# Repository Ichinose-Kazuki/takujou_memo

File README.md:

# takujou_memo

* サーバ側処理：server フォントのパスを変更しないとWindowsで使えないので注意してください
* ESP32側コード最終版：tcp_and_spiffs_and_eink

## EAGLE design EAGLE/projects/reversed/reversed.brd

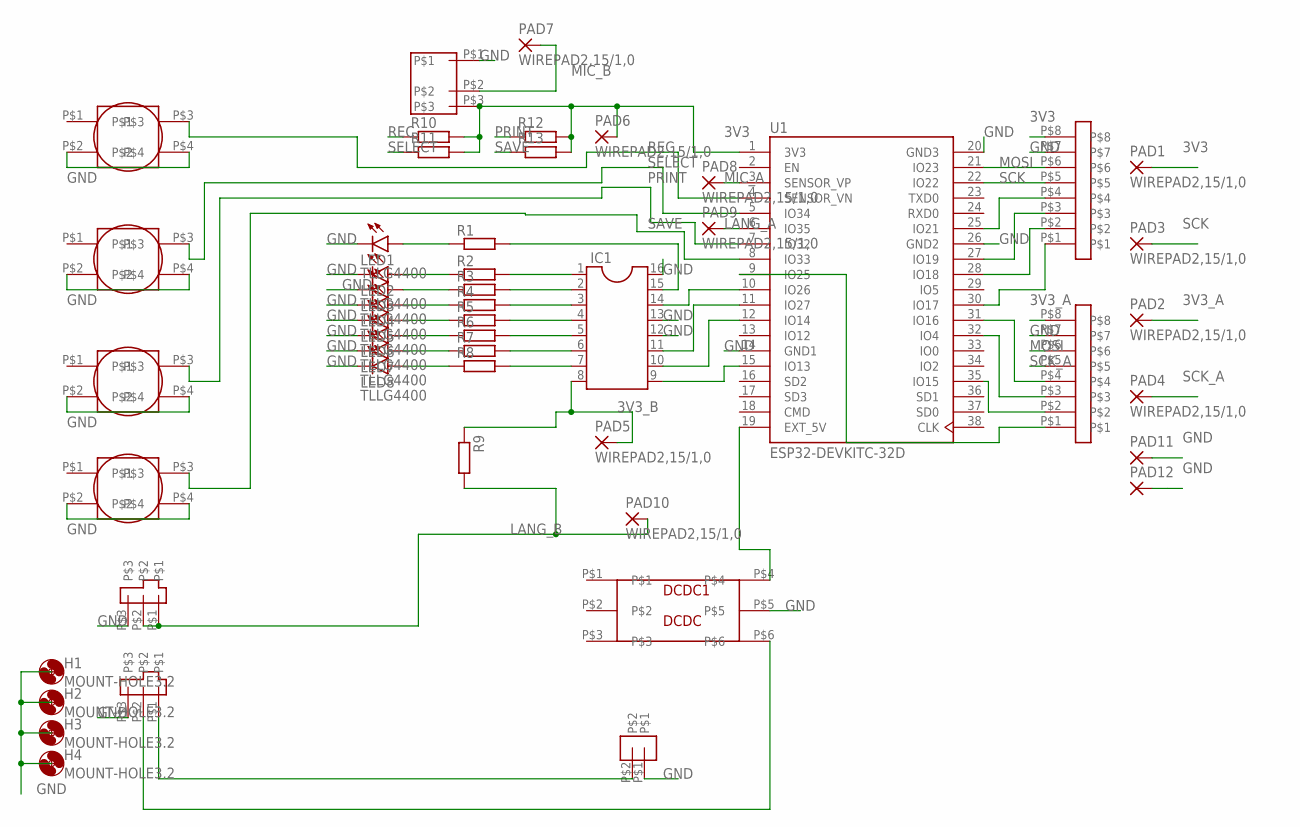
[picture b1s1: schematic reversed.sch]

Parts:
BATTERY1: BATTERY
DCDC1: DCDC
DISPLAY1, DISPLAY2: DISPLAY
H1, H2, H3, H4: MOUNT-HOLE3.2; 3,2
IC1: DIL16S; SOCKET-16
LED1, LED2, LED3, LED4, LED5, LED6, LED7, LED8: TLLG4400; LED3MM
MIC1: MIC
PAD1, PAD2, PAD3, PAD4, PAD5, PAD6, PAD7, PAD8, PAD9, PAD10: WIREPAD2,15/1,0; 2,15/1,0
PAD11, PAD12: 2,15/1,0
R1, R2, R3, R4, R5, R6, R7, R8: SMK
R9, R10, R11, R12, R13: R-EU_0207/10; 0207/10
SWITCH1, SWITCH2, SWITCH3, SWITCH4: SWITCH
TOGGLE1, TOGGLE2: TOGGLE
U1: ESP32-DEVKITC-32D; MODULE_ESP32-DEVKITC-32D

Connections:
3V3: DISPLAY1.P$8, MIC1.P$3, PAD1.1, PAD6.1, R10.2, R11.2, R12.2, R13.2, U1.1 (3V3)
3V3_A: DISPLAY2.P$8, PAD2.1
3V3_B: IC1.8, PAD5.1, R9.1
GND: BATTERY1.P$1, DCDC1.P$5, DISPLAY1.P$7, DISPLAY2.P$7, IC1.12, IC1.13, IC1.16, LED1.K (C), LED2.K (C), LED3.K (C), LED4.K (C), LED5.K (C), LED6.K (C), LED7.K (C), LED8.K (C), MIC1.P$1, PAD11.1, PAD12.1, SWITCH1.P$2, SWITCH1.P$4, SWITCH2.P$2, SWITCH2.P$4, SWITCH3.P$2, SWITCH3.P$4, SWITCH4.P$2, SWITCH4.P$4, TOGGLE1.P$3, TOGGLE2.P$3, U1.14 (GND1), U1.20 (GND3), U1.26 (GND2)
LANG_A: PAD9.1, U1.6 (IO35)
LANG_B: PAD10.1, R9.2, TOGGLE1.P$1, TOGGLE1.P$2
MIC_A: PAD8.1, U1.3 (SENSOR_VP)
MIC_B: MIC1.P$2, PAD7.1
MOSI: DISPLAY1.P$6, DISPLAY2.P$6, U1.21 (IO23)
unnamed: DISPLAY1.P$4, U1.25 (IO21)
unnamed: DISPLAY1.P$3, U1.27 (IO19)
unnamed: DISPLAY1.P$2, U1.28 (IO18)
unnamed: DISPLAY1.P$1, U1.30 (IO17)
unnamed: DISPLAY2.P$4, U1.31 (IO16)
unnamed: DISPLAY2.P$3, U1.32 (IO4)
unnamed: DISPLAY2.P$2, U1.35 (IO15)
unnamed: DISPLAY2.P$1, U1.9 (IO25)
unnamed: IC1.9, U1.15 (IO13)
unnamed: IC1.10, U1.12 (IO14)
unnamed: IC1.11, U1.11 (IO27)
unnamed: IC1.14, U1.10 (IO26)
unnamed: IC1.15, R1.1
unnamed: IC1.1, R2.1
unnamed: IC1.2, R3.1
unnamed: IC1.3, R4.1
unnamed: IC1.4, R5.1
unnamed: IC1.5, R6.1
unnamed: IC1.6, R7.1
unnamed: IC1.7, R8.1
unnamed: DCDC1.P$4, U1.19 (EXT_5V)
unnamed: LED1.A, R1.2
unnamed: LED2.A, R2.2
unnamed: LED3.A, R3.2
unnamed: LED4.A, R4.2
unnamed: LED5.A, R5.2
unnamed: LED6.A, R6.2
unnamed: LED7.A, R7.2
unnamed: LED8.A, R8.2
unnamed: DCDC1.P$6, TOGGLE2.P$2
unnamed: BATTERY1.P$2, TOGGLE2.P$1
PRINT: R12.1, SWITCH3.P$3, U1.7 (IO32)
REC: R10.1, SWITCH1.P$3, U1.4 (SENSOR_VN)
SAVE: R13.1, SWITCH4.P$3, U1.8 (IO33)
SCK: DISPLAY1.P$5, PAD3.1, U1.22 (IO22)
SCK_A: DISPLAY2.P$5, PAD4.1
SELECT: R11.1, SWITCH2.P$3, U1.5 (IO34)

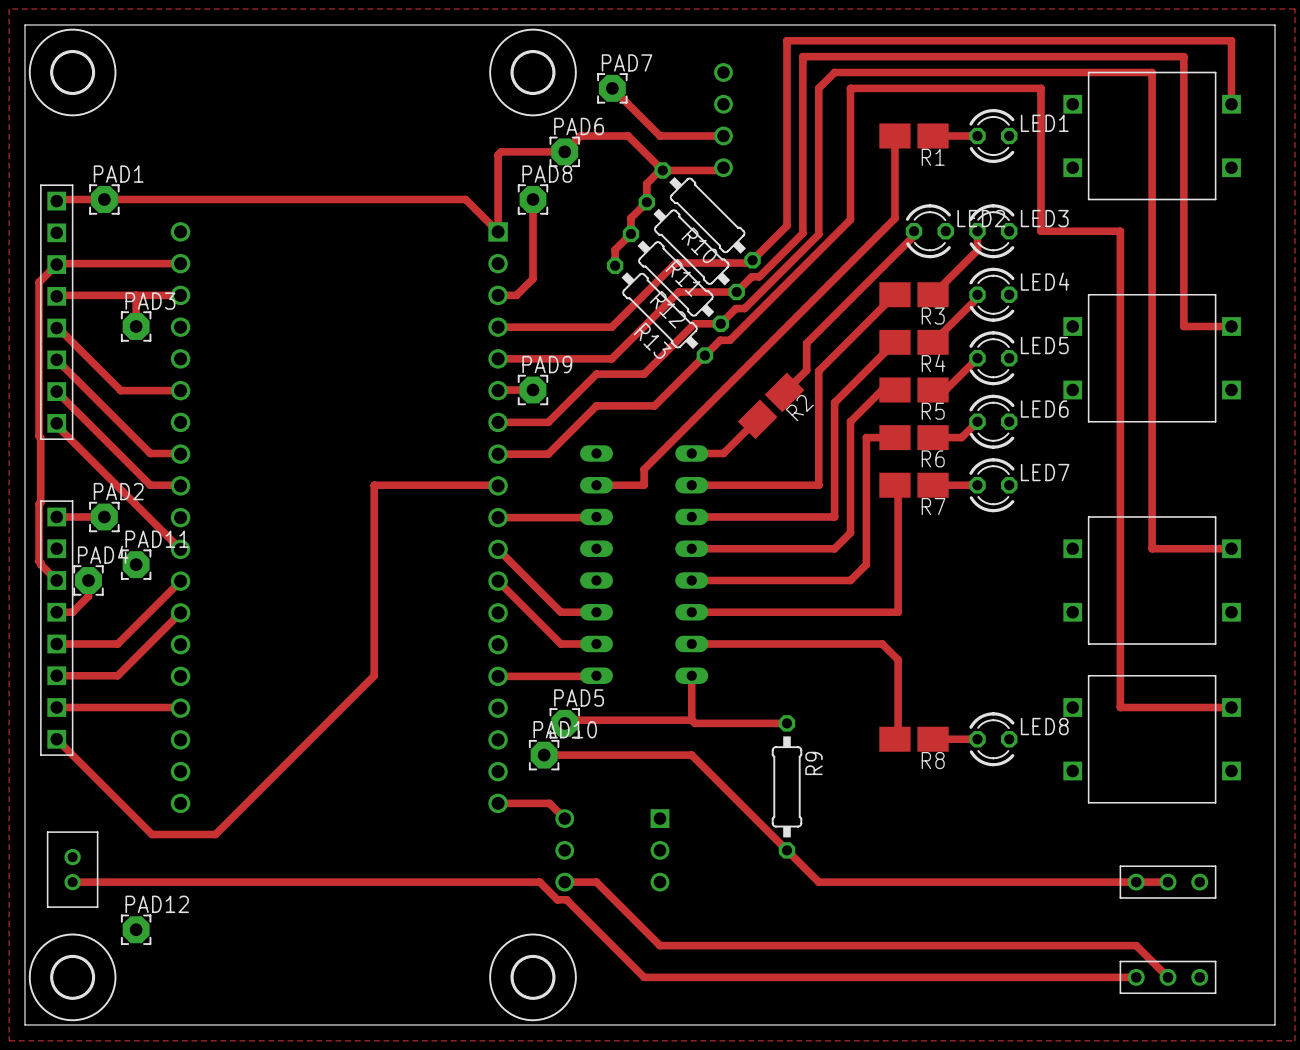
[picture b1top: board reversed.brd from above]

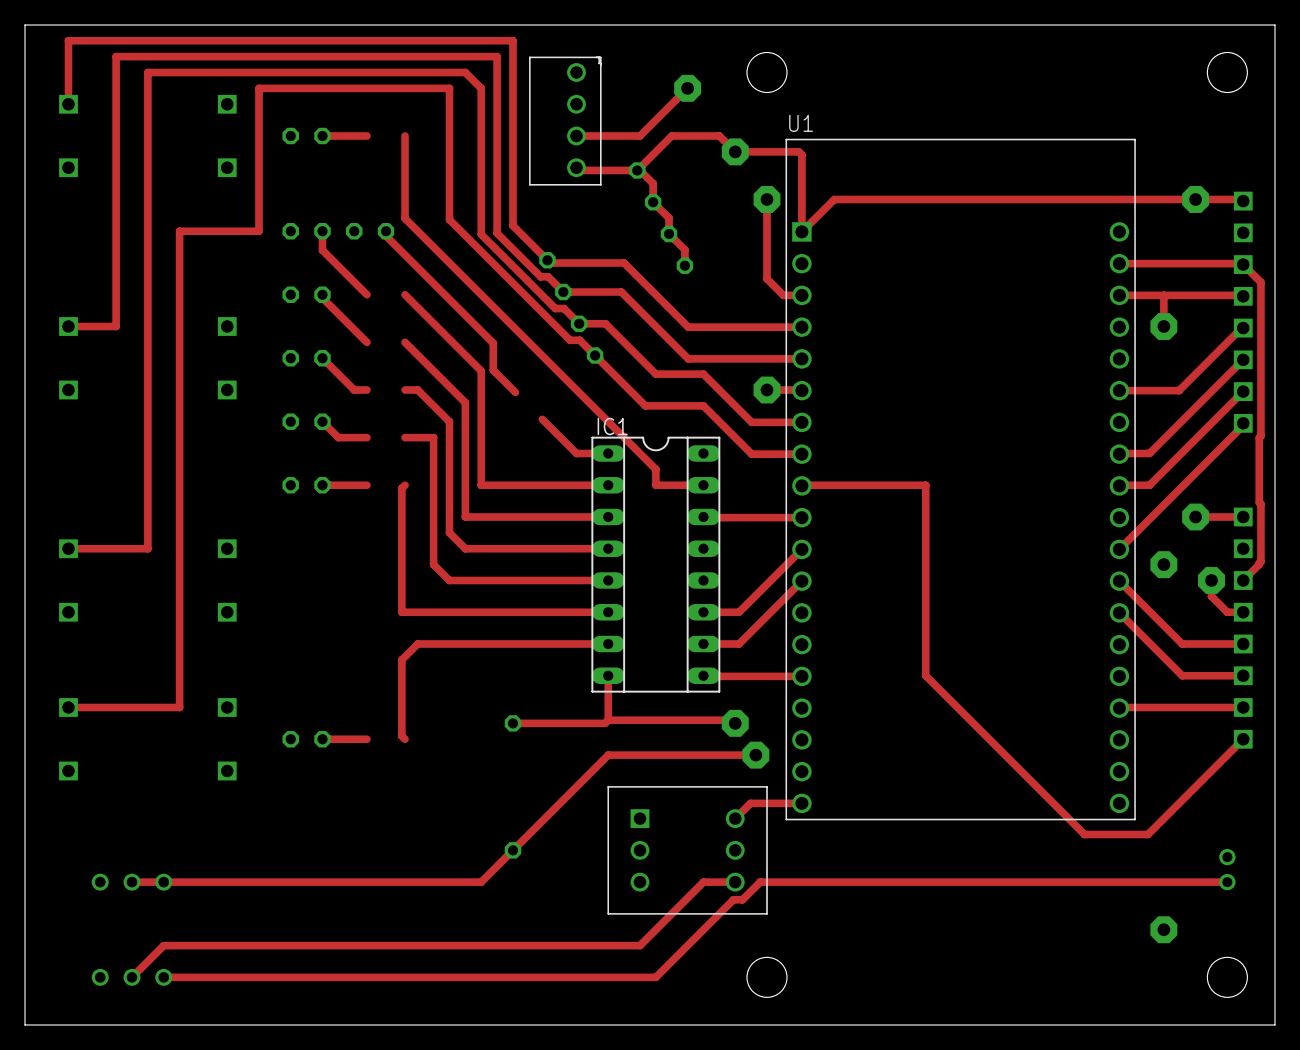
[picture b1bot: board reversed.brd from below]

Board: 2 copper layers, 100.0 x 80.0 mm, 50 parts (4 on the bottom side), 46 nets.
